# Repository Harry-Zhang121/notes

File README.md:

# notes
All of my notes in markdown.

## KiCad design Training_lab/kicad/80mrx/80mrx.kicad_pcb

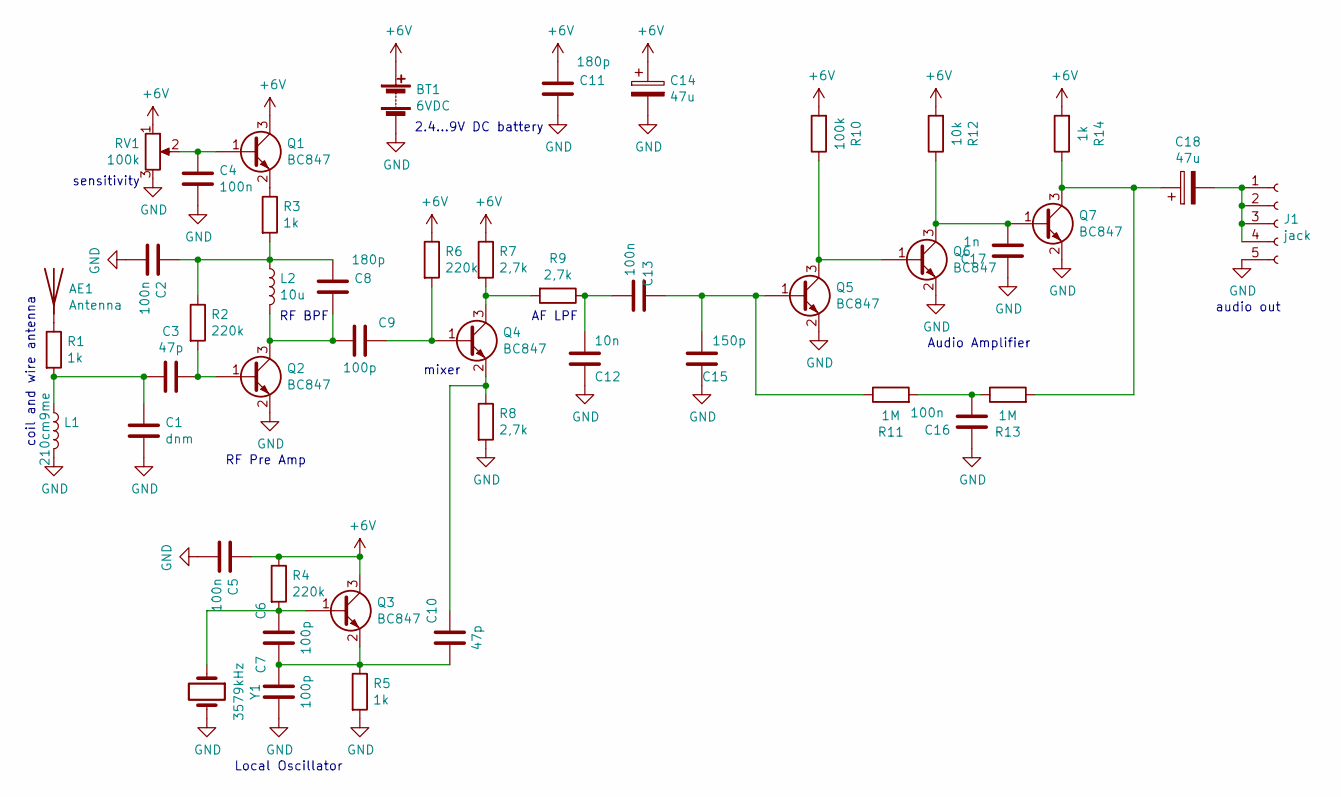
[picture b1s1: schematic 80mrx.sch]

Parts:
AE1: Antenna; PinHeader_1x01_P2.54mm_Vertical
BT1: 6VDC; PinHeader_1x02_P2.54mm_Vertical
C1: dnm; C_0805_2012Metric_Pad1.18x1.45mm_HandSolder
C2, C4, C5, C13, C16: 100n; C_0805_2012Metric_Pad1.18x1.45mm_HandSolder
C3, C10: 47p; C_0805_2012Metric_Pad1.18x1.45mm_HandSolder
C6, C7, C9: 100p; C_0805_2012Metric_Pad1.18x1.45mm_HandSolder
C8, C11: 180p; C_0805_2012Metric_Pad1.18x1.45mm_HandSolder
C12: 10n; C_0805_2012Metric_Pad1.18x1.45mm_HandSolder
C14, C18: 47u; C_1206_3216Metric_Pad1.33x1.80mm_HandSolder
C15: 150p; C_0805_2012Metric_Pad1.18x1.45mm_HandSolder
C17: 1n; C_0805_2012Metric_Pad1.18x1.45mm_HandSolder
J1: jack
L1: 210cm9me; PinHeader_1x02_P2.54mm_Vertical
L2: 10u; L_1206_3216Metric_Pad1.22x1.90mm_HandSolder
Q1, Q2, Q3, Q4, Q5, Q6, Q7: BC847; SOT-23
R1, R3, R5, R14: 1k; R_0805_2012Metric_Pad1.20x1.40mm_HandSolder
R2, R4, R6: 220k; R_0805_2012Metric_Pad1.20x1.40mm_HandSolder
R7, R8, R9: 2,7k; R_0805_2012Metric_Pad1.20x1.40mm_HandSolder
R10: 100k; R_0805_2012Metric_Pad1.20x1.40mm_HandSolder
R11, R13: 1M; R_0805_2012Metric_Pad1.20x1.40mm_HandSolder
R12: 10k; R_0805_2012Metric_Pad1.20x1.40mm_HandSolder
RV1: 100k; poti
Y1: 3579kHz; Crystal_SMD_HC49-SD_HandSoldering

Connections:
+6V: BT1.1 (+), C5.1, C11.1, C14.1, Q1.3 (C), Q3.3 (C), R4.1, R6.1, R7.1, R10.2, R12.2, R14.2, RV1.1
GND: BT1.2 (-), C1.2, C2.2, C4.2, C5.2, C7.1, C11.2, C12.2, C14.2, C15.1, C16.1, C17.1, J1.5, L1.2, Q2.2 (E), Q5.2 (E), Q6.2 (E), Q7.2 (E), R5.2, R8.2, RV1.3, Y1.2
unnamed: AE1.1, R1.1
unnamed: C1.1, C3.2, L1.1, R1.2
unnamed: C2.1, C8.1, L2.1, R2.1, R3.2
unnamed: C3.1, Q2.1 (B), R2.2
unnamed: C4.1, Q1.1 (B), RV1.2
unnamed: C6.2, Q3.1 (B), R4.2, Y1.1
unnamed: C8.2, C9.1, L2.2, Q2.3 (C)
unnamed: C9.2, Q4.1 (B), R6.2
unnamed: C6.1, C7.2, C10.1, Q3.2 (E), R5.1
unnamed: C10.2, Q4.2 (E), R8.1
unnamed: C12.1, C13.2, R9.1
unnamed: C13.1, C15.2, Q5.1 (B), R11.1
unnamed: C16.2, R11.2, R13.1
unnamed: C17.2, Q6.3 (C), Q7.1 (B), R12.1
unnamed: C18.1, Q7.3 (C), R13.2, R14.1
unnamed: C18.2, J1.1, J1.2, J1.3, J1.4
unnamed: Q1.2 (E), R3.1
unnamed: Q4.3 (C), R7.2, R9.2
unnamed: Q5.3 (C), Q6.1 (B), R10.1

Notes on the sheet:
sensitivity
audio out
coil and wire antenna
RF Pre Amp
RF BPF
mixer
AF LPF
Local Oscillator
Audio Amplifier
2.4...9V DC battery

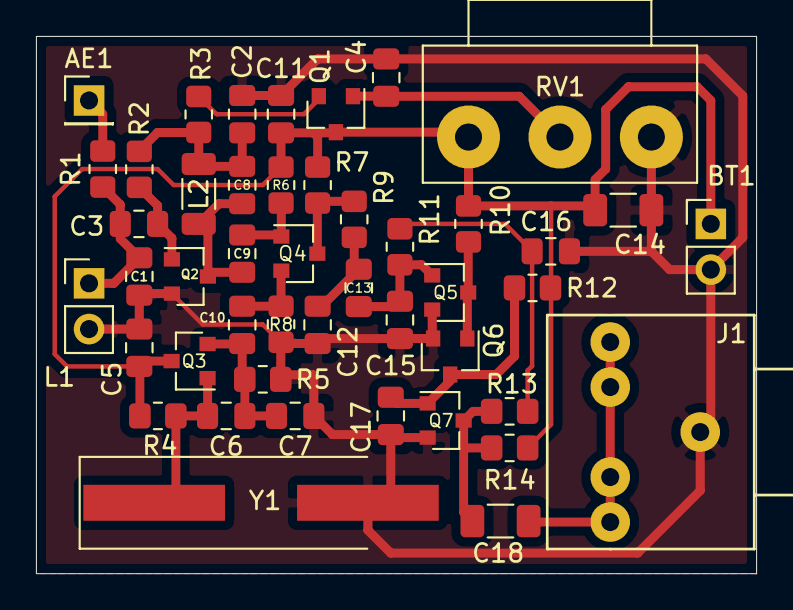
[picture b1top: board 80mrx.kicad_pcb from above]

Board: 2 copper layers, 40.0 x 29.8 mm, 46 parts (0 on the bottom side), 21 nets.

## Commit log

2022-03-14 Uploaded old notes
2022-03-28 Environmental note for the first midterm
2022-04-01 Added notes
2022-04-17 Added Micro&Macro and obsidian config
2022-04-17 update report
2022-04-23 update assignment
2022-04-23 Assignment finished
2022-11-06 upload files
2022-11-24 update notes
2022-11-25 Update notes. Finished homework
2022-11-28 Added traning laboratory files
2022-11-30 Update on training lab report.
2022-11-30 Update lab report
2022-12-02 Renamed labreport. Added 3 figures
2022-12-02 Seperate report into two parts
2022-12-12 Labreport finished
2022-12-14 Added training lab presentation
2023-03-01 Add security and privacy note
2023-05-13 vault backup: 2023-05-13 18:46:19
2023-06-15 vault backup: 2023-06-15 14:28:24
2023-06-15 vault backup: 2023-06-15 14:28:34
2023-06-15 Add simbiota-cloud presentation
2023-06-15 Update Ielts nots
